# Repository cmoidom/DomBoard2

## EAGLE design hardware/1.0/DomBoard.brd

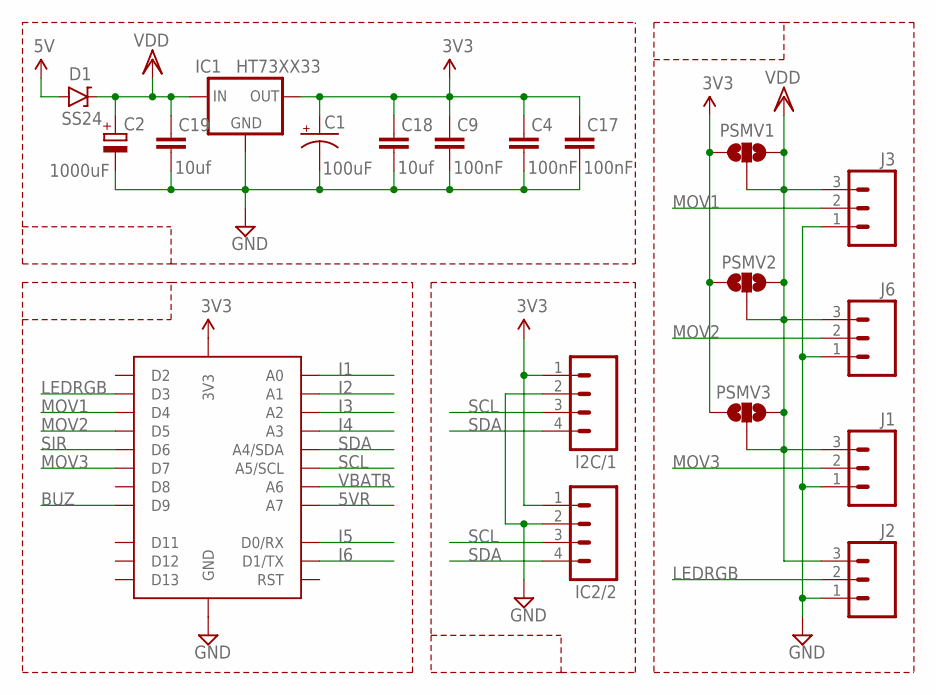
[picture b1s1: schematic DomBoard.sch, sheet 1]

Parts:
C1: 100uF; EIA3528-KIT
C2: 1000uF; E5-8,5
C4, C9, C17: 100nF; C0805K
C18, C19: 10uf; C0805K
D1: SS24; DO-214AA(1)
I2C/1: M04PTH; 1X04
IC1: HT73XX33; SOT-89
IC2/2: M04PTH; 1X04
J1, J2, J3, J6: M03JST-PTH-VERT; JST-3-PTH-VERT
PROMINI69: PROMINI69
PSMV1, PSMV2, PSMV3: JUMPER-PAD-3-NC_BY_TRACE; PAD-JUMPER-3-3OF3_NC_BY_TRACE_YES_SILK_FULL_BOX

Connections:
3.3V: C1.A (+), C4.2, C9.2, C17.2, C18.2, I2C/1.1, IC1.1 (OUT), IC2/2.1, PROMINI69.3V3, PSMV1.1, PSMV2.1, PSMV3.1; also elsewhere on the board
5V: D1.A; also elsewhere on the board
5VR: PROMINI69.A7; also elsewhere on the board
BUZ: PROMINI69.D9; also elsewhere on the board
GND: C1.C (-), C2.-, C4.1, C9.1, C17.1, C18.1, C19.1, I2C/1.2, IC1.2 (GND), IC2/2.2, J1.1, J2.1, J3.1, J6.1, PROMINI69.GND; also elsewhere on the board
I1: PROMINI69.A0; also elsewhere on the board
I2: PROMINI69.A1; also elsewhere on the board
I3: PROMINI69.A2; also elsewhere on the board
I4: PROMINI69.A3; also elsewhere on the board
I5: PROMINI69.D0 (D0/RX); also elsewhere on the board
I6: PROMINI69.D1 (D1/TX); also elsewhere on the board
LEDRGB: J2.2, PROMINI69.D3
MOV1: J3.2, PROMINI69.D4
MOV2: J6.2, PROMINI69.D5
MOV3: J1.2, PROMINI69.D7
SCL: I2C/1.3, IC2/2.3, PROMINI69.A5 (A5/SCL); also elsewhere on the board
SDA: I2C/1.4, IC2/2.4, PROMINI69.A4 (A4/SDA); also elsewhere on the board
SIR: PROMINI69.D6; also elsewhere on the board
VBATR: PROMINI69.A6; also elsewhere on the board
VDD: C2.+, C19.2, D1.C, IC1.3 (IN), IC1.4 (IN), J1.3, J2.3, J3.3, J6.3, PSMV1.2, PSMV1.3, PSMV2.2, PSMV2.3, PSMV3.2, PSMV3.3; also elsewhere on the board

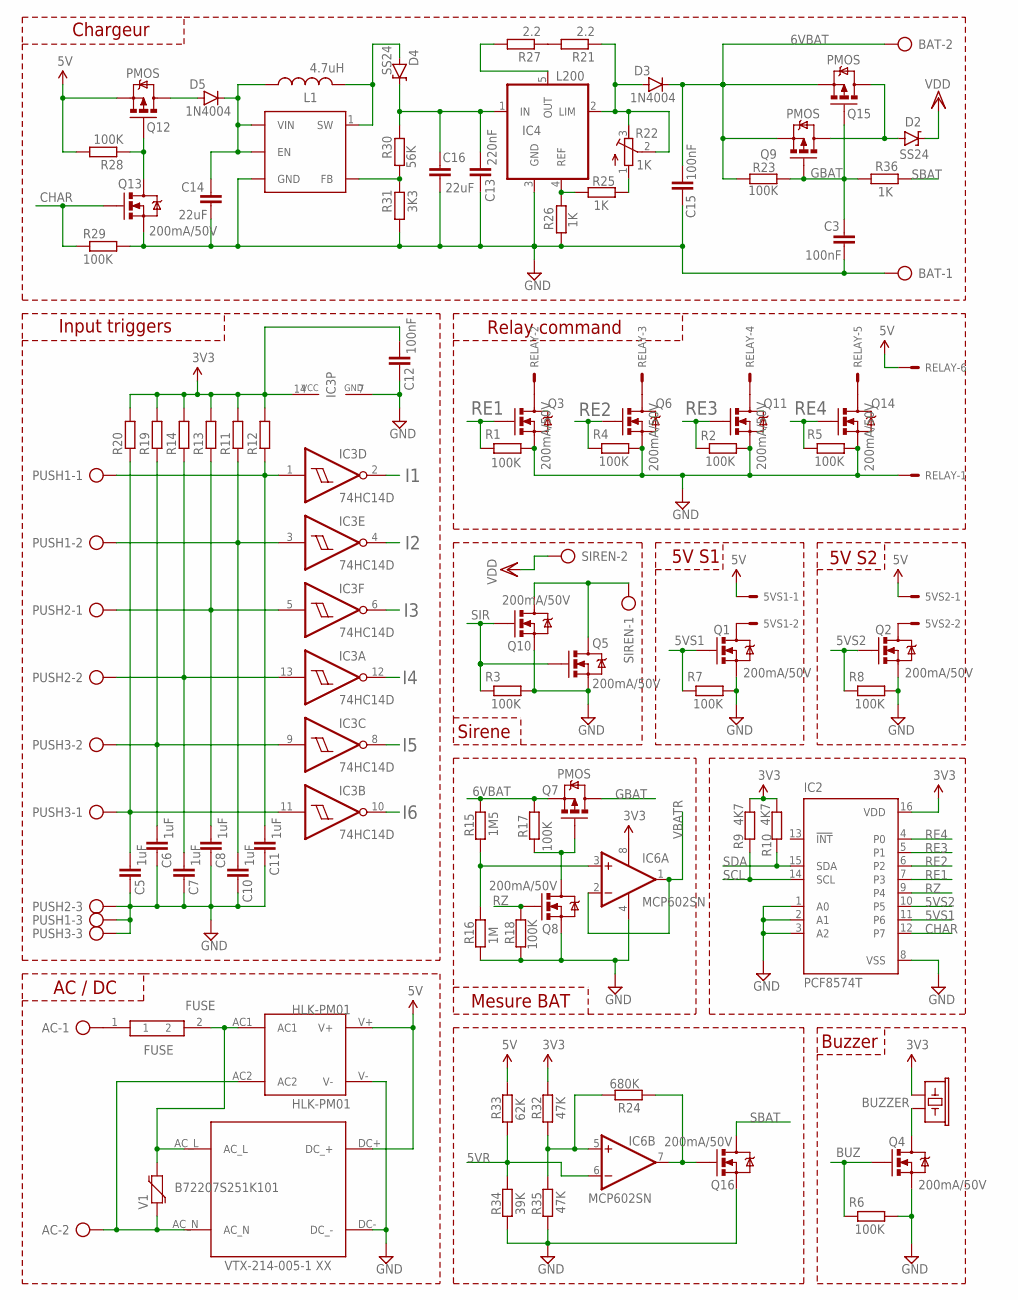
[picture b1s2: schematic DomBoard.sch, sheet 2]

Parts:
5VS1, 5VS2: 22-23-2021
AC: AK500/2
BAT: AK500/2
BUZZER: BUZZER; BUZZER-12MM
C3, C12, C15: 100nF; C0805K
C5, C6, C7, C8, C10, C11: 1uF; C0805K
C13: 220nF; C0805K
C14, C16: 22uF; C0805K
D2, D4: SS24; DO-214AA(1)
D3, D5: 1N4004; DO-214AA(1)
FUSE: FUSE; FUSE_BEL_RST5_5A
HLK-PM01: HLK-PM01; HILINK_HLK-PM01
IC2: PCF8574T; SO16W
IC3: 74HC14D; SO14
IC4: L200; L200S
IC5: SX1308; SOT23-6
IC6: MCP602SN; SO08
L1: 4.7uH; INDUC1
PUSH1, PUSH2, PUSH3: AK500/3
Q1, Q2, Q3, Q4, Q5, Q6, Q8, Q10, Q11, Q13, Q14, Q16: 200mA/50V; SOT23-3
Q7, Q9, Q12, Q15: PMOS; SOT23-3
R1, R2, R3, R4, R5, R6, R7, R8, R17, R18, R23, R28, R29: 100K; R0805
R9, R10: 4K7; R0805
R11, R12, R13, R14, R19, R20: R-EUR0805; R0805
R15: 1M5; R0805
R16: 1M; R0805
R21, R27: 2.2; R0805
R22: 1K; RTRIM3296W
R24: 680K; R0805
R25, R26, R36: 1K; R0805
R30: 56K; M0805
R31: 3K3; M0805
R32, R35: 47K; R0805
R33: 62K; R0805
R34: 39K; R0805
RELAY: 22-23-2061
SIREN: AK500/2
V1: B72207S251K101; VARISTOR_B72207S251K101
VTX1: VTX-214-005-1XX

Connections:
3.3V: BUZZER.+ (1), C12.1, IC2.16 (VDD), IC3.14 (VCC), IC6.8 (V+), R9.1, R10.1, R11.2, R12.2, R13.2, R14.2, R19.2, R20.2, R32.2; also elsewhere on the board
5V: 5VS1.1, 5VS2.1, HLK-PM01.V+, Q12.2 (S), R28.2, R33.2, RELAY.6, VTX1.DC+ (DC_+); also elsewhere on the board
5VR: IC6.6 (-IN), R33.1, R34.2; also elsewhere on the board
5VS1: IC2.11 (P6), Q1.1 (G), R7.2
5VS2: IC2.10 (P5), Q2.1 (G), R8.2
6VBAT: BAT.2, C15.1, D3.C, Q7.2 (S), Q9.2 (S), Q15.2 (S), R15.1, R17.1, R23.2
BATC: D2.A, Q9.3 (D), Q15.3 (D)
BUZ: Q4.1 (G), R6.2; also elsewhere on the board
CHAR: IC2.12 (P7), Q13.1 (G), R29.1
GBAT: C3.1, Q7.3 (D), Q9.1 (G), Q15.1 (G), R23.1, R36.1
GND: BAT.1, C3.2, C5.2, C6.2, C7.2, C8.2, C10.2, C11.2, C12.2, C13.2, C14.2, C15.2, C16.2, HLK-PM01.V-, IC2.1 (A0), IC2.2 (A1), IC2.3 (A2), IC2.8 (VSS), IC3.7 (GND), IC4.3 (GND), IC5.2 (GND), IC6.4 (V-), PUSH1.3, PUSH2.3, PUSH3.3, Q1.2 (S), Q2.2 (S), Q3.2 (S), Q4.2 (S), Q5.2 (S), Q6.2 (S), Q8.2 (S), Q10.2 (S), Q11.2 (S), Q13.2 (S), Q14.2 (S), Q16.2 (S), R1.1, R2.1, R3.1, R4.1, R5.1, R6.1, R7.1, R8.1, R16.2, R18.1, R26.2, R29.2, R31.1, R34.1, R35.1, RELAY.1, VTX1.DC- (DC_-); also elsewhere on the board
I1: IC3.2 (O); also elsewhere on the board
I2: IC3.4 (O); also elsewhere on the board
I3: IC3.6 (O); also elsewhere on the board
I4: IC3.12 (O); also elsewhere on the board
I5: IC3.8 (O); also elsewhere on the board
I6: IC3.10 (O); also elsewhere on the board
unnamed: BUZZER.- (2), Q4.3 (D)
unnamed: IC6.7 (OUT), Q16.1 (G), R24.1
unnamed: C11.1, IC3.1 (I), PUSH1.1, R12.1
unnamed: C10.1, IC3.3 (I), PUSH1.2, R11.1
unnamed: Q7.1 (G), Q8.3 (D), R17.2
unnamed: Q3.3 (D), RELAY.2
unnamed: Q6.3 (D), RELAY.3
unnamed: AC.1, FUSE.1
unnamed: Q5.3 (D), Q10.3 (D), SIREN.1
unnamed: 5VS1.2, Q1.3 (D)
unnamed: C8.1, IC3.5 (I), PUSH2.1, R13.1
unnamed: 5VS2.2, Q2.3 (D)
unnamed: C7.1, IC3.13 (I), PUSH2.2, R14.1
unnamed: C6.1, IC3.9 (I), PUSH3.2, R19.1
unnamed: C5.1, IC3.11 (I), PUSH3.1, R20.1
unnamed: R21.2, R27.1
unnamed: IC4.5 (OUT), R27.2
unnamed: R22.1 (A), R25.2
unnamed: IC6.5 (+IN), R24.2, R32.1, R35.2
unnamed: Q11.3 (D), RELAY.4
unnamed: Q14.3 (D), RELAY.5
unnamed: C13.1, C16.1, D4.C, IC4.1 (IN), R30.2
unnamed: D5.A, Q12.3 (D)
unnamed: IC4.4 (REF), R25.1, R26.1
unnamed: D3.A, IC4.2 (LIM), R21.1, R22.2 (S), R22.3 (E)
unnamed: Q12.1 (G), Q13.3 (D), R28.1
unnamed: AC.2, HLK-PM01.AC2, V1.1, VTX1.AC_N
unnamed: C14.1, D5.C, IC5.4 (EN), IC5.5 (VIN), L1.1
unnamed: D4.A, IC5.1 (SW), L1.2
unnamed: IC5.3 (FB), R30.1, R31.2
unnamed: FUSE.2, HLK-PM01.AC1, V1.2, VTX1.AC_L
RE1: IC2.7 (P3), Q3.1 (G), R1.2
RE2: IC2.6 (P2), Q6.1 (G), R4.2
RE3: IC2.5 (P1), Q11.1 (G), R2.2
RE4: IC2.4 (P0), Q14.1 (G), R5.2
RZ: IC2.9 (P4), Q8.1 (G), R18.2
SBAT: Q16.3 (D), R36.2
SCL: IC2.14 (SCL), R9.2; also elsewhere on the board
SDA: IC2.15 (SDA), R10.2; also elsewhere on the board
SIR: Q5.1 (G), Q10.1 (G), R3.2; also elsewhere on the board
VBATR: IC6.1 (OUT), IC6.2 (-IN); also elsewhere on the board
VBR: IC6.3 (+IN), R15.2, R16.1
VDD: D2.C, SIREN.2; also elsewhere on the board

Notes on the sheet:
Relay command
Input triggers
Sirene
Buzzer
AC / DC
Mesure BAT
Chargeur
5V S1
5V S2

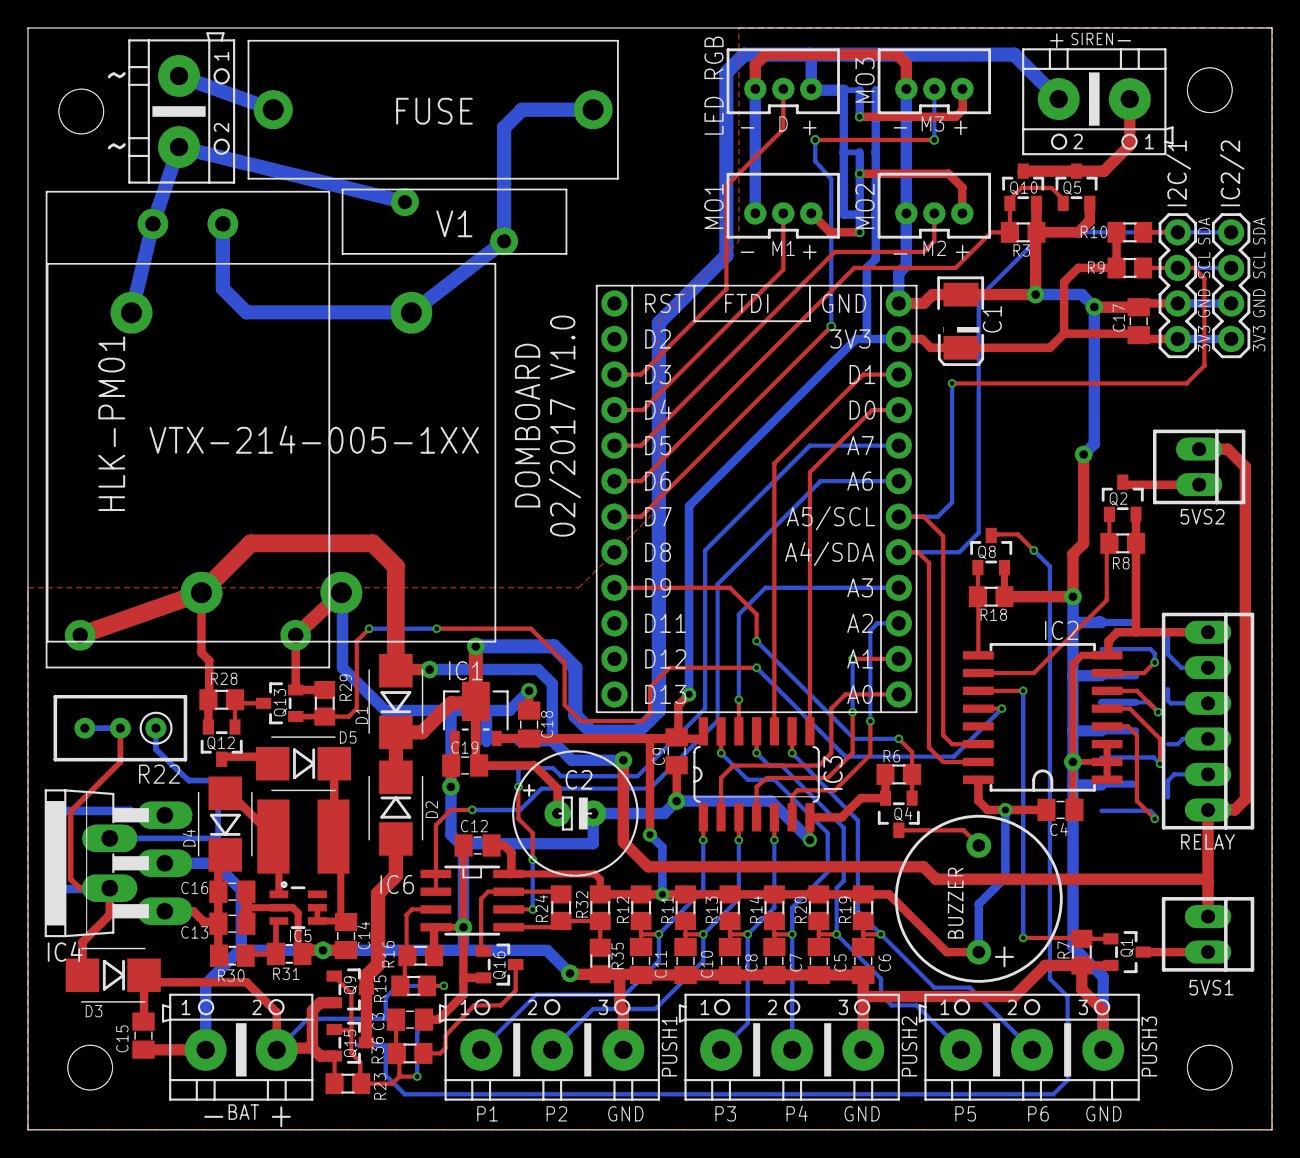
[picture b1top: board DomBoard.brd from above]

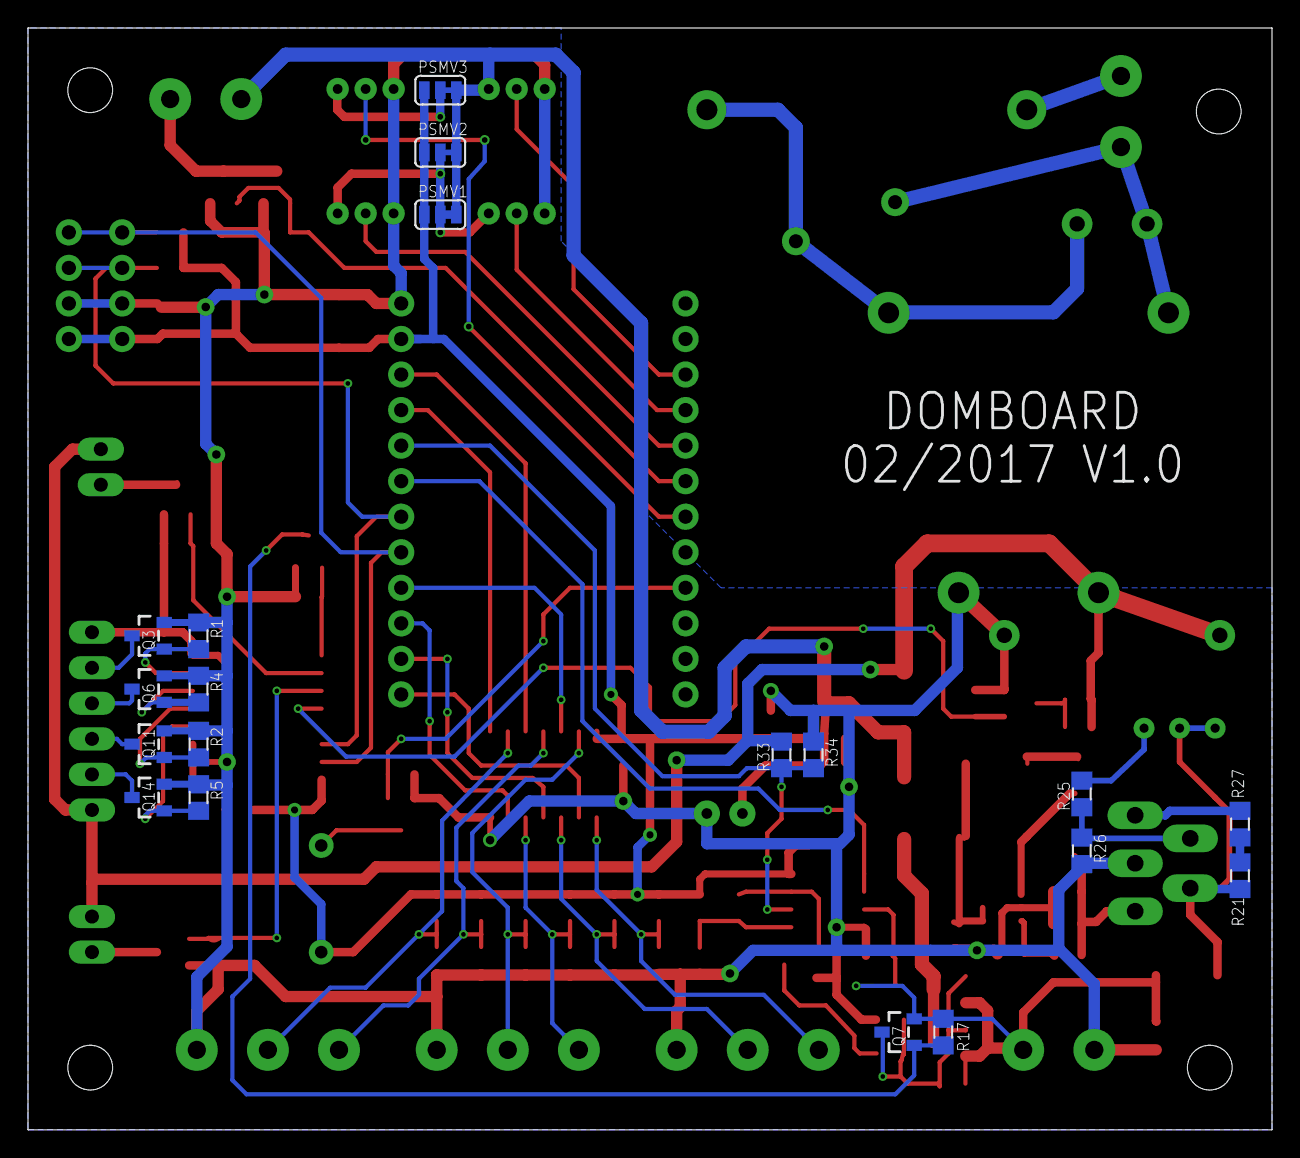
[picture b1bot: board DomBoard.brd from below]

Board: 2 copper layers, 88.9 x 78.7 mm, 107 parts (19 on the bottom side), 64 nets.

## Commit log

2017-02-05 :circus_tent: Added .gitattributes & .gitignore files
2017-02-05 DomBoard
    First version.

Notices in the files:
parts and their libraries:
SparkFun-Connectors: Licensing: CC v3.0 Share-Alike You are welcome to use this library for commercial purposes.
SparkFun-Capacitors: Licensing: Creative Commons ShareAlike 4.0 International - https://creativecommons.org/licenses/by-sa/4.0
